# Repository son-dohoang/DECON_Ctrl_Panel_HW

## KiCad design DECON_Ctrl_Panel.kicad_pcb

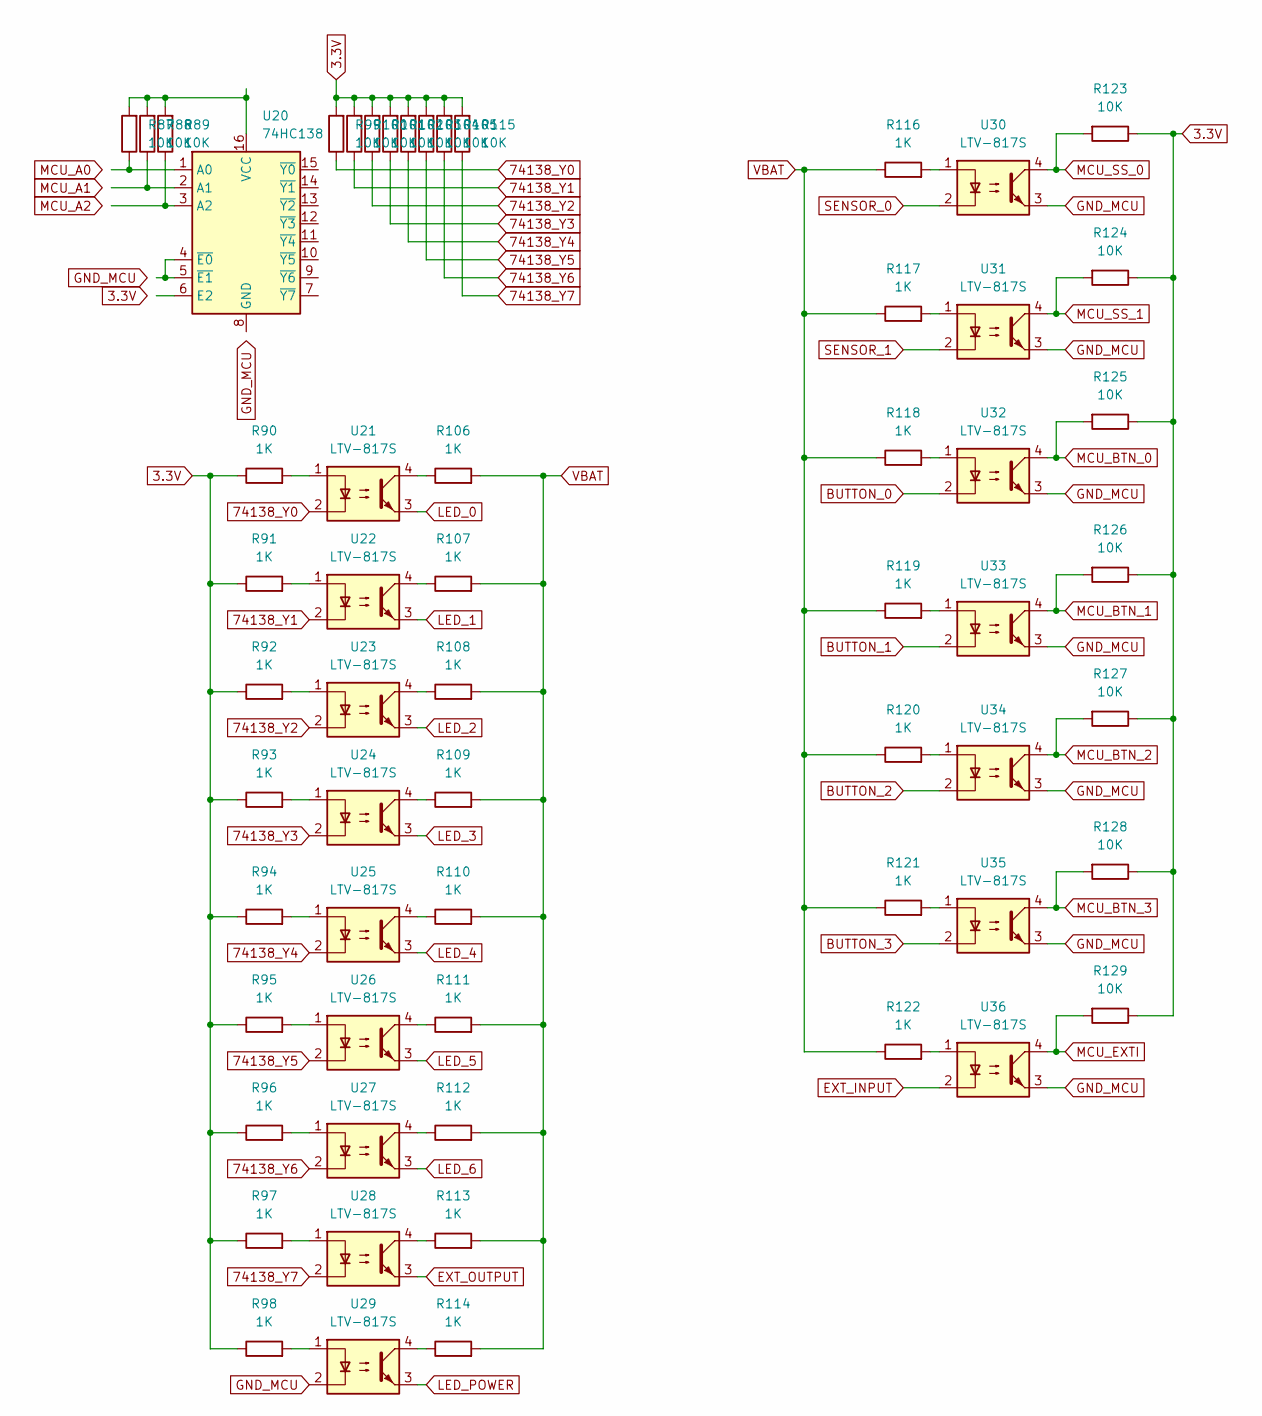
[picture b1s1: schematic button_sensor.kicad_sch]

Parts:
R87, R88, R89, R99, R100, R101, R102, R103, R104, R105, R115, R123, R124, R125, R126, R127, R128, R129: 10K; R_0805_2012Metric
R90, R91, R92, R93, R94, R95, R96, R97, R98, R106, R107, R108, R109, R110, R111, R112, R113, R114, R116, R117, R118, R119, R120, R121, R122: 1K; R_0805_2012Metric
U20: 74HC138; SOIC-16_3.9x9.9mm_P1.27mm
U21, U22, U23, U24, U25, U26, U27, U28, U29, U30, U31, U32, U33, U34, U35, U36: LTV-817S; SMDIP-4_W9.53mm

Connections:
3.3V: R90.1, R91.1, R92.1, R93.1, R94.1, R95.1, R96.1, R97.1, R98.1, R99.2, R100.2, R101.2, R102.2, R103.2, R104.2, R105.2, R115.2, R123.1, R124.1, R125.1, R126.1, R127.1, R128.1, R129.1; also elsewhere on the board
74138_Y0: R99.1, U21.2; also elsewhere on the board
74138_Y1: R100.1, U22.2; also elsewhere on the board
74138_Y2: R101.1, U23.2; also elsewhere on the board
74138_Y3: R102.1, U24.2; also elsewhere on the board
74138_Y4: R103.1, U25.2; also elsewhere on the board
74138_Y5: R104.1, U26.2; also elsewhere on the board
74138_Y6: R105.1, U27.2; also elsewhere on the board
74138_Y7: R115.1, U28.2; also elsewhere on the board
BUTTON_0: U32.2; also elsewhere on the board
BUTTON_1: U33.2; also elsewhere on the board
BUTTON_2: U34.2; also elsewhere on the board
BUTTON_3: U35.2; also elsewhere on the board
EXT_INPUT: U36.2; also elsewhere on the board
EXT_OUTPUT: U28.3; also elsewhere on the board
GND_MCU: U29.2, U30.3, U31.3, U32.3, U33.3, U34.3, U35.3, U36.3; also elsewhere on the board
LED_0: U21.3; also elsewhere on the board
LED_1: U22.3; also elsewhere on the board
LED_2: U23.3; also elsewhere on the board
LED_3: U24.3; also elsewhere on the board
LED_4: U25.3; also elsewhere on the board
LED_5: U26.3; also elsewhere on the board
LED_6: U27.3; also elsewhere on the board
LED_POWER: U29.3; also elsewhere on the board
MCU_BTN_0: R125.2, U32.4; also elsewhere on the board
MCU_BTN_1: R126.2, U33.4; also elsewhere on the board
MCU_BTN_2: R127.2, U34.4; also elsewhere on the board
MCU_BTN_3: R128.2, U35.4; also elsewhere on the board
MCU_EXTI: R129.2, U36.4; also elsewhere on the board
MCU_SS_0: R123.2, U30.4; also elsewhere on the board
MCU_SS_1: R124.2, U31.4; also elsewhere on the board
unnamed: R87.1, U20.1 (A0)
unnamed: R87.2, R88.2, R89.2, U20.16 (VCC)
unnamed: R88.1, U20.2 (A1)
unnamed: R89.1, U20.3 (A2)
unnamed: R90.2, U21.1
unnamed: R91.2, U22.1
unnamed: R92.2, U23.1
unnamed: R93.2, U24.1
unnamed: R94.2, U25.1
unnamed: R95.2, U26.1
unnamed: R96.2, U27.1
unnamed: R97.2, U28.1
unnamed: R98.2, U29.1
unnamed: R106.1, U21.4
unnamed: R107.1, U22.4
unnamed: R108.1, U23.4
unnamed: R109.1, U24.4
unnamed: R110.1, U25.4
unnamed: R111.1, U26.4
unnamed: R112.1, U27.4
unnamed: R113.1, U28.4
unnamed: R114.1, U29.4
unnamed: R116.2, U30.1
unnamed: R117.2, U31.1
unnamed: R118.2, U32.1
unnamed: R119.2, U33.1
unnamed: R120.2, U34.1
unnamed: R121.2, U35.1
unnamed: R122.2, U36.1
unnamed: U20.4 (~E0), U20.5 (~E1)
SENSOR_0: U30.2; also elsewhere on the board
SENSOR_1: U31.2; also elsewhere on the board
VBAT: R106.2, R107.2, R108.2, R109.2, R110.2, R111.2, R112.2, R113.2, R114.2, R116.1, R117.1, R118.1, R119.1, R120.1, R121.1, R122.1; also elsewhere on the board

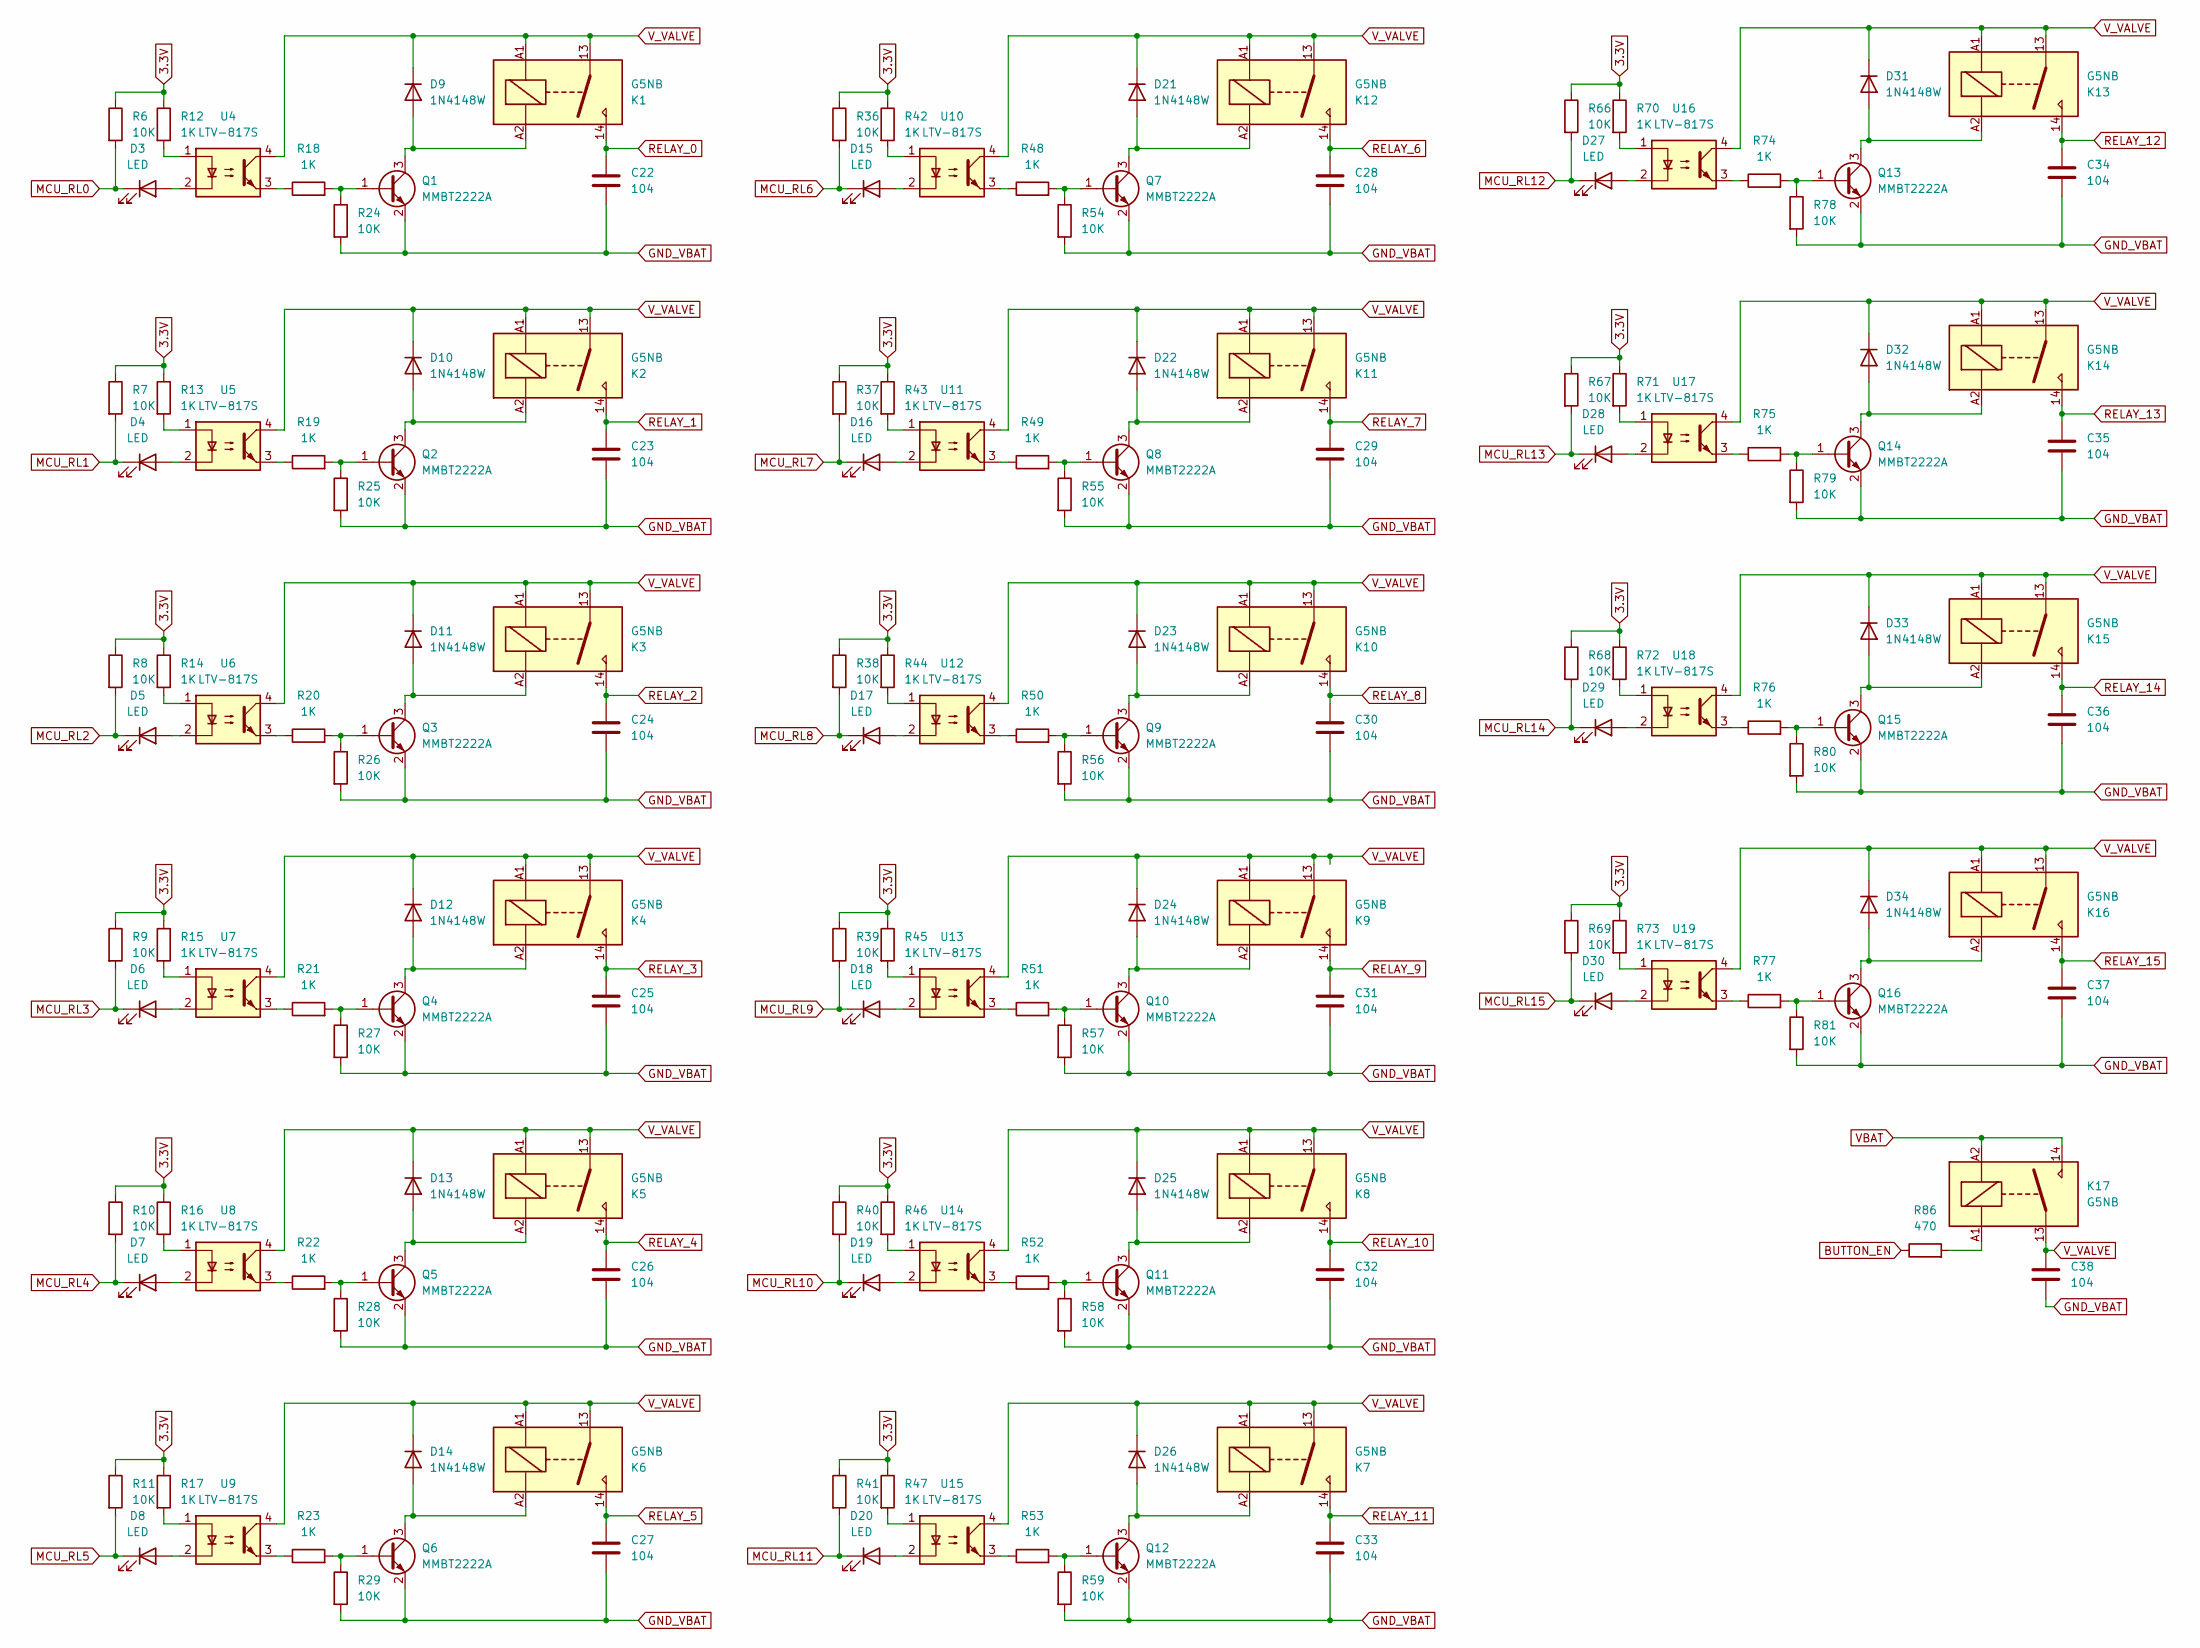
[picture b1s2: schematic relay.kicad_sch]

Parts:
C22, C23, C24, C25, C26, C27, C28, C29, C30, C31, C32, C33, C34, C35, C36, C37, C38: 104; C_0805_2012Metric
D3, D4, D5, D6, D7, D8, D15, D16, D17, D18, D19, D20, D27, D28, D29, D30: LED; LED_0805_2012Metric
D9, D10, D11, D12, D13, D14, D21, D22, D23, D24, D25, D26, D31, D32, D33, D34: 1N4148W; D_SOD-123
K1, K2, K3, K4, K5, K6, K7, K8, K9, K10, K11, K12, K13, K14, K15, K16, K17: G5NB; Relay_SPST_Omron_G5NB
Q1, Q2, Q3, Q4, Q5, Q6, Q7, Q8, Q9, Q10, Q11, Q12, Q13, Q14, Q15, Q16: MMBT2222A; SOT-23-3
R6, R7, R8, R9, R10, R11, R24, R25, R26, R27, R28, R29, R36, R37, R38, R39, R40, R41, R54, R55, R56, R57, R58, R59, R66, R67, R68, R69, R78, R79, R80, R81: 10K; R_0805_2012Metric
R12, R13, R14, R15, R16, R17, R18, R19, R20, R21, R22, R23, R42, R43, R44, R45, R46, R47, R48, R49, R50, R51, R52, R53, R70, R71, R72, R73, R74, R75, R76, R77: 1K; R_0805_2012Metric
R86: 470; R_0805_2012Metric
U4, U5, U6, U7, U8, U9, U10, U11, U12, U13, U14, U15, U16, U17, U18, U19: LTV-817S; SMDIP-4_W9.53mm

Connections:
3.3V: R6.1, R7.1, R8.1, R9.1, R10.1, R11.1, R12.1, R13.1, R14.1, R15.1, R16.1, R17.1, R36.1, R37.1, R38.1, R39.1, R40.1, R41.1, R42.1, R43.1, R44.1, R45.1, R46.1, R47.1, R66.1, R67.1, R68.1, R69.1, R70.1, R71.1, R72.1, R73.1; also elsewhere on the board
BUTTON_EN: R86.1; also elsewhere on the board
GND_VBAT: C22.2, C23.2, C24.2, C25.2, C26.2, C27.2, C28.2, C29.2, C30.2, C31.2, C32.2, C33.2, C34.2, C35.2, C36.2, C37.2, C38.2, Q1.2 (E), Q2.2 (E), Q3.2 (E), Q4.2 (E), Q5.2 (E), Q6.2 (E), Q7.2 (E), Q8.2 (E), Q9.2 (E), Q10.2 (E), Q11.2 (E), Q12.2 (E), Q13.2 (E), Q14.2 (E), Q15.2 (E), Q16.2 (E), R24.2, R25.2, R26.2, R27.2, R28.2, R29.2, R54.2, R55.2, R56.2, R57.2, R58.2, R59.2, R78.2, R79.2, R80.2, R81.2; also elsewhere on the board
MCU_RL0: D3.1 (K), R6.2; also elsewhere on the board
MCU_RL1: D4.1 (K), R7.2; also elsewhere on the board
MCU_RL2: D5.1 (K), R8.2; also elsewhere on the board
MCU_RL3: D6.1 (K), R9.2; also elsewhere on the board
MCU_RL4: D7.1 (K), R10.2; also elsewhere on the board
MCU_RL5: D8.1 (K), R11.2; also elsewhere on the board
MCU_RL6: D15.1 (K), R36.2; also elsewhere on the board
MCU_RL7: D16.1 (K), R37.2; also elsewhere on the board
MCU_RL8: D17.1 (K), R38.2; also elsewhere on the board
MCU_RL9: D18.1 (K), R39.2; also elsewhere on the board
MCU_RL10: D19.1 (K), R40.2; also elsewhere on the board
MCU_RL11: D20.1 (K), R41.2; also elsewhere on the board
MCU_RL12: D27.1 (K), R66.2; also elsewhere on the board
MCU_RL13: D28.1 (K), R67.2; also elsewhere on the board
MCU_RL14: D29.1 (K), R68.2; also elsewhere on the board
MCU_RL15: D30.1 (K), R69.2; also elsewhere on the board
unnamed: D3.2 (A), U4.2
unnamed: D4.2 (A), U5.2
unnamed: D5.2 (A), U6.2
unnamed: D6.2 (A), U7.2
unnamed: D7.2 (A), U8.2
unnamed: D8.2 (A), U9.2
unnamed: D9.2 (A), K1.A2, Q1.3 (C)
unnamed: D10.2 (A), K2.A2, Q2.3 (C)
unnamed: D11.2 (A), K3.A2, Q3.3 (C)
unnamed: D12.2 (A), K4.A2, Q4.3 (C)
unnamed: D13.2 (A), K5.A2, Q5.3 (C)
unnamed: D14.2 (A), K6.A2, Q6.3 (C)
unnamed: D15.2 (A), U10.2
unnamed: D16.2 (A), U11.2
unnamed: D17.2 (A), U12.2
unnamed: D18.2 (A), U13.2
unnamed: D19.2 (A), U14.2
unnamed: D20.2 (A), U15.2
unnamed: D21.2 (A), K12.A2, Q7.3 (C)
unnamed: D22.2 (A), K11.A2, Q8.3 (C)
unnamed: D23.2 (A), K10.A2, Q9.3 (C)
unnamed: D24.2 (A), K9.A2, Q10.3 (C)
unnamed: D25.2 (A), K8.A2, Q11.3 (C)
unnamed: D26.2 (A), K7.A2, Q12.3 (C)
unnamed: D27.2 (A), U16.2
unnamed: D28.2 (A), U17.2
unnamed: D29.2 (A), U18.2
unnamed: D30.2 (A), U19.2
unnamed: D31.2 (A), K13.A2, Q13.3 (C)
unnamed: D32.2 (A), K14.A2, Q14.3 (C)
unnamed: D33.2 (A), K15.A2, Q15.3 (C)
unnamed: D34.2 (A), K16.A2, Q16.3 (C)
unnamed: K17.A1, R86.2
unnamed: Q1.1 (B), R18.2, R24.1
unnamed: Q2.1 (B), R19.2, R25.1
unnamed: Q3.1 (B), R20.2, R26.1
unnamed: Q4.1 (B), R21.2, R27.1
unnamed: Q5.1 (B), R22.2, R28.1
unnamed: Q6.1 (B), R23.2, R29.1
unnamed: Q7.1 (B), R48.2, R54.1
unnamed: Q8.1 (B), R49.2, R55.1
unnamed: Q9.1 (B), R50.2, R56.1
unnamed: Q10.1 (B), R51.2, R57.1
unnamed: Q11.1 (B), R52.2, R58.1
unnamed: Q12.1 (B), R53.2, R59.1
unnamed: Q13.1 (B), R74.2, R78.1
unnamed: Q14.1 (B), R75.2, R79.1
unnamed: Q15.1 (B), R76.2, R80.1
unnamed: Q16.1 (B), R77.2, R81.1
unnamed: R12.2, U4.1
unnamed: R13.2, U5.1
unnamed: R14.2, U6.1
unnamed: R15.2, U7.1
unnamed: R16.2, U8.1
unnamed: R17.2, U9.1
unnamed: R18.1, U4.3
unnamed: R19.1, U5.3
unnamed: R20.1, U6.3
unnamed: R21.1, U7.3
unnamed: R22.1, U8.3
unnamed: R23.1, U9.3
unnamed: R42.2, U10.1
unnamed: R43.2, U11.1
unnamed: R44.2, U12.1
unnamed: R45.2, U13.1
unnamed: R46.2, U14.1
unnamed: R47.2, U15.1
unnamed: R48.1, U10.3
unnamed: R49.1, U11.3
unnamed: R50.1, U12.3
unnamed: R51.1, U13.3
unnamed: R52.1, U14.3
unnamed: R53.1, U15.3
unnamed: R70.2, U16.1
unnamed: R71.2, U17.1
unnamed: R72.2, U18.1
unnamed: R73.2, U19.1
unnamed: R74.1, U16.3
unnamed: R75.1, U17.3
unnamed: R76.1, U18.3
unnamed: R77.1, U19.3
RELAY_0: C22.1, K1.14; also elsewhere on the board
RELAY_1: C23.1, K2.14; also elsewhere on the board
RELAY_2: C24.1, K3.14; also elsewhere on the board
RELAY_3: C25.1, K4.14; also elsewhere on the board
RELAY_4: C26.1, K5.14; also elsewhere on the board
RELAY_5: C27.1, K6.14; also elsewhere on the board
RELAY_6: C28.1, K12.14; also elsewhere on the board
RELAY_7: C29.1, K11.14; also elsewhere on the board
RELAY_8: C30.1, K10.14; also elsewhere on the board
RELAY_9: C31.1, K9.14; also elsewhere on the board
RELAY_10: C32.1, K8.14; also elsewhere on the board
RELAY_11: C33.1, K7.14; also elsewhere on the board
RELAY_12: C34.1, K13.14; also elsewhere on the board
RELAY_13: C35.1, K14.14; also elsewhere on the board
RELAY_14: C36.1, K15.14; also elsewhere on the board
RELAY_15: C37.1, K16.14; also elsewhere on the board
VBAT: K17.14, K17.A2; also elsewhere on the board
V_VALVE: C38.1, D9.1 (K), D10.1 (K), D11.1 (K), D12.1 (K), D13.1 (K), D14.1 (K), D21.1 (K), D22.1 (K), D23.1 (K), D24.1 (K), D25.1 (K), D26.1 (K), D31.1 (K), D32.1 (K), D33.1 (K), D34.1 (K), K1.13, K1.A1, K2.13, K2.A1, K3.13, K3.A1, K4.13, K4.A1, K5.13, K5.A1, K6.13, K6.A1, K7.13, K7.A1, K8.13, K8.A1, K9.13, K9.A1, K10.13, K10.A1, K11.13, K11.A1, K12.13, K12.A1, K13.13, K13.A1, K14.13, K14.A1, K15.13, K15.A1, K16.13, K16.A1, K17.13, U4.4, U5.4, U6.4, U7.4, U8.4, U9.4, U10.4, U11.4, U12.4, U13.4, U14.4, U15.4, U16.4, U17.4, U18.4, U19.4

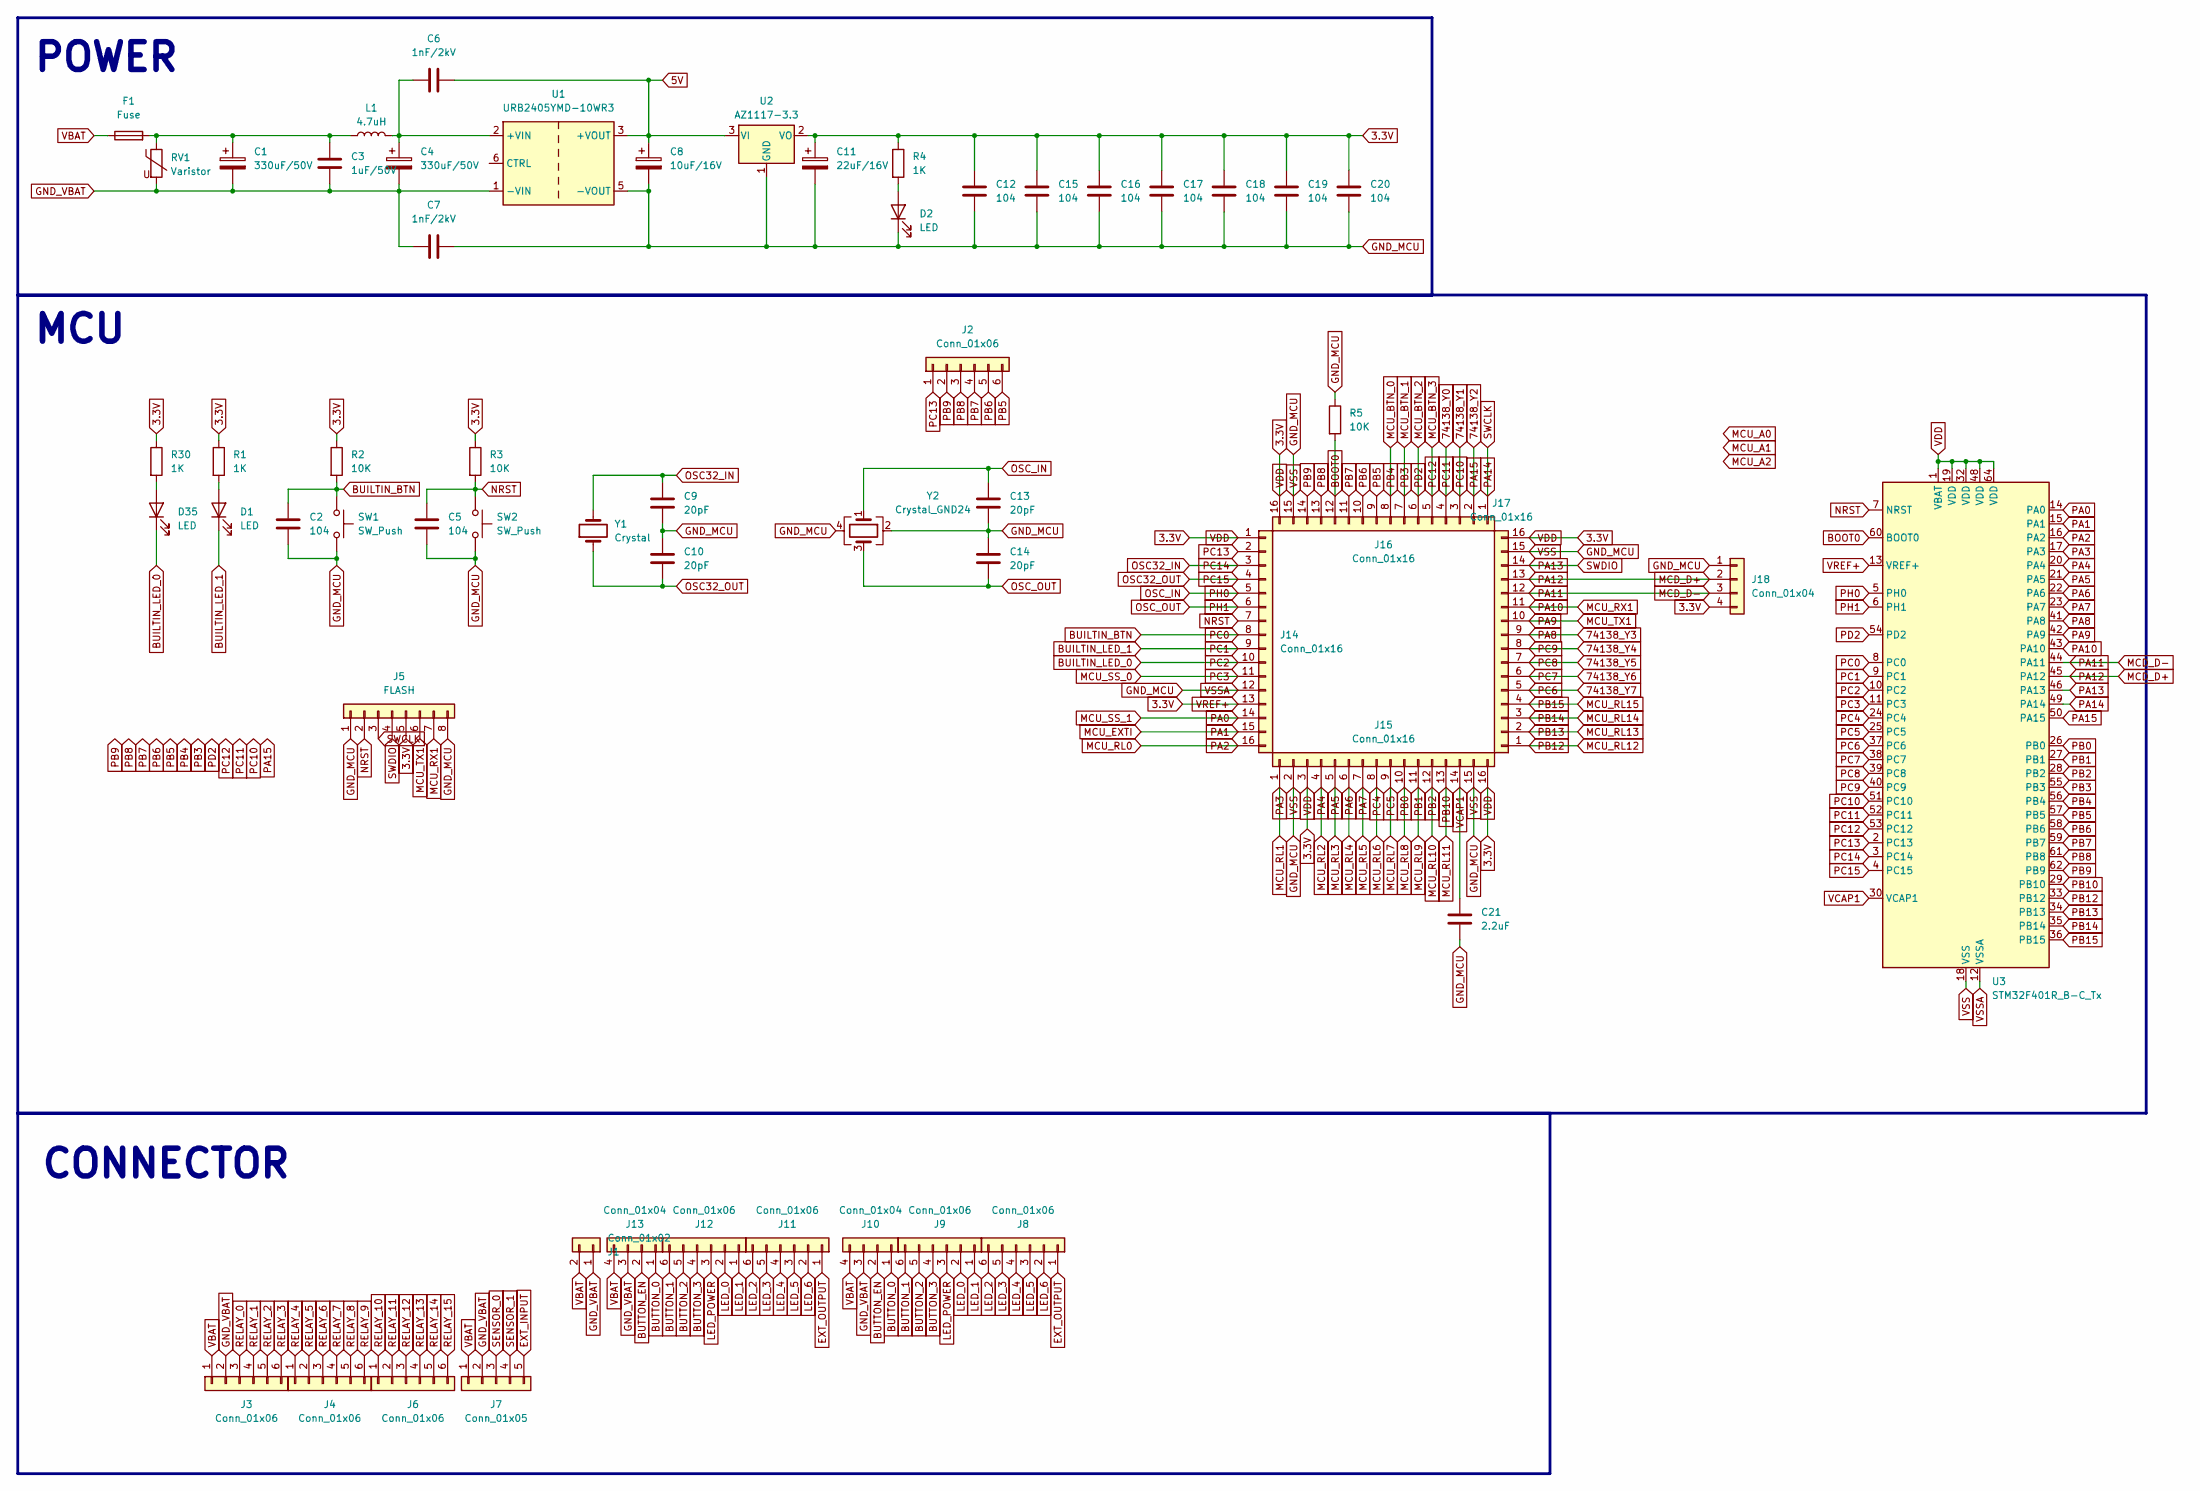
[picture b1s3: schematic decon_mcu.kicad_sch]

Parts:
C1, C4: 330uF/50V; CP_Elec_10x10.5
C2, C5, C12, C15, C16, C17, C18, C19, C20: 104; C_0805_2012Metric
C3: 1uF/50V; C_0805_2012Metric
C6, C7: 1nF/2kV; C_Disc_D5.0mm_W2.5mm_P5.00mm
C8: 10uF/16V; CP_Elec_4x5.4
C9, C10, C13, C14: 20pF; C_0805_2012Metric
C11: 22uF/16V; CP_Elec_4x5.4
C21: 2.2uF; C_0805_2012Metric
D1, D2, D35: LED; LED_0805_2012Metric
F1: Fuse; Fuseholder_Clip-5x20mm_Eaton_1A5601-01_Inline_P20.80x6.76mm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
J1: Conn_01x02; TerminalBlock_MetzConnect_Type086_RT03402HBLC_1x02_P3.81mm_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
J2: Conn_01x06; PinHeader_1x06_P2.54mm_Vertical
J3, J4, J6, J8, J9, J11, J12: Conn_01x06; TerminalBlock_MetzConnect_Type086_RT03406HBLC_1x06_P3.81mm_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
J5: FLASH; PinHeader_1x08_P2.54mm_Vertical
J7: Conn_01x05; TerminalBlock_MetzConnect_Type086_RT03405HBLC_1x05_P3.81mm_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
J10, J13: Conn_01x04; TerminalBlock_MetzConnect_Type086_RT03404HBLC_1x04_P3.81mm_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
J14, J15, J16, J17: Conn_01x16
J18: Conn_01x04; PinHeader_1x04_P2.54mm_Vertical
L1: 4.7uH; L_APV_APH0630
R1, R4, R30: 1K; R_0805_2012Metric
R2, R3, R5: 10K; R_0805_2012Metric
RV1: Varistor; RV_Disc_D7mm_W3.4mm_P5mm
SW1, SW2: SW_Push; SW_SPST_CK_RS282G05A3
U1: URB2405YMD-10WR3
U2: AZ1117-3.3; SOT-223-3_TabPin2
U3: STM32F401R_B-C_Tx; LQFP-64_10x10mm_P0.5mm
Y1: Crystal; Crystal_SMD_3215-2Pin_3.2x1.5mm
Y2: Crystal_GND24; Crystal_SMD_3225-4Pin_3.2x2.5mm

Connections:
3.3V: C11.1, C12.2, C15.2, C16.2, C17.2, C18.2, C19.2, C20.2, J5.5, J14.1, J14.13, J15.3, J15.16, J16.16, J17.16, J18.4, R1.1, R2.1, R3.1, R4.1, R30.1, U2.2 (VO), U3.1 (VBAT), U3.13 (VREF+), U3.19 (VDD), U3.32 (VDD), U3.48 (VDD), U3.64 (VDD); also elsewhere on the board
5V: C6.2, C8.1, U1.3 (+VOUT), U2.3 (VI)
74138_Y0: J16.4, U3.52 (PC11); also elsewhere on the board
74138_Y1: J16.3, U3.51 (PC10); also elsewhere on the board
74138_Y2: J16.2, U3.50 (PA15); also elsewhere on the board
74138_Y3: J17.9, U3.41 (PA8); also elsewhere on the board
74138_Y4: J17.8, U3.40 (PC9); also elsewhere on the board
74138_Y5: J17.7, U3.39 (PC8); also elsewhere on the board
74138_Y6: J17.6, U3.38 (PC7); also elsewhere on the board
74138_Y7: J17.5, U3.37 (PC6); also elsewhere on the board
BOOT0: J16.12, R5.2, U3.60 (BOOT0)
BUILTIN_BTN: C2.1, J14.8, R2.2, SW1.1, U3.8 (PC0)
BUILTIN_LED_0: D35.1 (K), J14.10, U3.10 (PC2)
BUILTIN_LED_1: D1.1 (K), J14.9, U3.9 (PC1)
BUTTON_0: J10.1, J13.1; also elsewhere on the board
BUTTON_1: J9.6, J12.6; also elsewhere on the board
BUTTON_2: J9.5, J12.5; also elsewhere on the board
BUTTON_3: J9.4, J12.4; also elsewhere on the board
BUTTON_EN: J10.2, J13.2; also elsewhere on the board
EXT_INPUT: J7.5; also elsewhere on the board
EXT_OUTPUT: J8.1, J11.1; also elsewhere on the board
GND_MCU: C2.2, C5.2, C7.2, C8.2, C9.2, C10.1, C11.2, C12.1, C13.1, C14.1, C15.1, C16.1, C17.1, C18.1, C19.1, C20.1, C21.2, D2.1 (K), J5.1, J5.8, J14.12, J15.2, J15.15, J16.15, J17.15, J18.1, R5.1, SW1.2, SW2.2, U1.5 (-VOUT), U2.1 (GND), U3.12 (VSSA), U3.18 (VSS), U3.31 (VSS), U3.47 (VSS), U3.63 (VSS), Y2.2, Y2.4; also elsewhere on the board
GND_VBAT: C1.2, C3.2, C4.2, C7.1, J1.1, J3.2, J7.2, J10.3, J13.3, RV1.2, U1.1 (-VIN); also elsewhere on the board
LED_0: J9.2, J12.2; also elsewhere on the board
LED_1: J9.1, J12.1; also elsewhere on the board
LED_2: J8.6, J11.6; also elsewhere on the board
LED_3: J8.5, J11.5; also elsewhere on the board
LED_4: J8.4, J11.4; also elsewhere on the board
LED_5: J8.3, J11.3; also elsewhere on the board
LED_6: J8.2, J11.2; also elsewhere on the board
LED_POWER: J9.3, J12.3; also elsewhere on the board
MCD_D+: J17.13, J18.2, U3.45 (PA12)
MCD_D-: J17.12, J18.3, U3.44 (PA11)
MCU_BTN_0: J16.8, U3.56 (PB4); also elsewhere on the board
MCU_BTN_1: J16.7, U3.55 (PB3); also elsewhere on the board
MCU_BTN_2: J16.6, U3.54 (PD2); also elsewhere on the board
MCU_BTN_3: J16.5, U3.53 (PC12); also elsewhere on the board
MCU_EXTI: J14.15, U3.15 (PA1); also elsewhere on the board
MCU_RL0: J14.16, U3.16 (PA2); also elsewhere on the board
MCU_RL1: J15.1, U3.17 (PA3); also elsewhere on the board
MCU_RL2: J15.4, U3.20 (PA4); also elsewhere on the board
MCU_RL3: J15.5, U3.21 (PA5); also elsewhere on the board
MCU_RL4: J15.6, U3.22 (PA6); also elsewhere on the board
MCU_RL5: J15.7, U3.23 (PA7); also elsewhere on the board
MCU_RL6: J15.8, U3.24 (PC4); also elsewhere on the board
MCU_RL7: J15.9, U3.25 (PC5); also elsewhere on the board
MCU_RL8: J15.10, U3.26 (PB0); also elsewhere on the board
MCU_RL9: J15.11, U3.27 (PB1); also elsewhere on the board
MCU_RL10: J15.12, U3.28 (PB2); also elsewhere on the board
MCU_RL11: J15.13, U3.29 (PB10); also elsewhere on the board
MCU_RL12: J17.1, U3.33 (PB12); also elsewhere on the board
MCU_RL13: J17.2, U3.34 (PB13); also elsewhere on the board
MCU_RL14: J17.3, U3.35 (PB14); also elsewhere on the board
MCU_RL15: J17.4, U3.36 (PB15); also elsewhere on the board
MCU_RX1: J5.7, J17.11, U3.43 (PA10)
MCU_SS_0: J14.11, U3.11 (PC3); also elsewhere on the board
MCU_SS_1: J14.14, U3.14 (PA0); also elsewhere on the board
MCU_TX1: J5.6, J17.10, U3.42 (PA9)
NRST: C5.1, J5.2, J14.7, R3.2, SW2.1, U3.7 (NRST)
unnamed: C1.1, C3.1, F1.2, L1.1, RV1.1
unnamed: D1.2 (A), R1.2
unnamed: D2.2 (A), R4.2
unnamed: D35.2 (A), R30.2
unnamed: C4.1, C6.1, L1.2, U1.2 (+VIN)
OSC32_IN: C9.1, J14.3, U3.3 (PC14), Y1.2
OSC32_OUT: C10.2, J14.4, U3.4 (PC15), Y1.1
OSC_IN: C13.2, J14.5, U3.5 (PH0), Y2.1
OSC_OUT: C14.2, J14.6, U3.6 (PH1), Y2.3
PA13: J5.4, J17.14, U3.46 (PA13)
PA14: J5.3, J16.1, U3.49 (PA14)
PB5: J2.6, J16.9, U3.57 (PB5)
PB6: J2.5, J16.10, U3.58 (PB6)
PB7: J2.4, J16.11, U3.59 (PB7)
PB8: J2.3, J16.13, U3.61 (PB8)
PB9: J2.2, J16.14, U3.62 (PB9)
PC13: J2.1, J14.2, U3.2 (PC13)
RELAY_0: J3.3; also elsewhere on the board
RELAY_1: J3.4; also elsewhere on the board
RELAY_2: J3.5; also elsewhere on the board
RELAY_3: J3.6; also elsewhere on the board
RELAY_4: J4.1; also elsewhere on the board
RELAY_5: J4.2; also elsewhere on the board
RELAY_6: J4.3; also elsewhere on the board
RELAY_7: J4.4; also elsewhere on the board
RELAY_8: J4.5; also elsewhere on the board
RELAY_9: J4.6; also elsewhere on the board
RELAY_10: J6.1; also elsewhere on the board
RELAY_11: J6.2; also elsewhere on the board
RELAY_12: J6.3; also elsewhere on the board
RELAY_13: J6.4; also elsewhere on the board
RELAY_14: J6.5; also elsewhere on the board
RELAY_15: J6.6; also elsewhere on the board
SENSOR_0: J7.3; also elsewhere on the board
SENSOR_1: J7.4; also elsewhere on the board
VBAT: F1.1, J1.2, J3.1, J7.1, J10.4, J13.4; also elsewhere on the board
VCAP1: C21.1, J15.14, U3.30 (VCAP1)

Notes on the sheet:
CONNECTOR
POWER
MCU

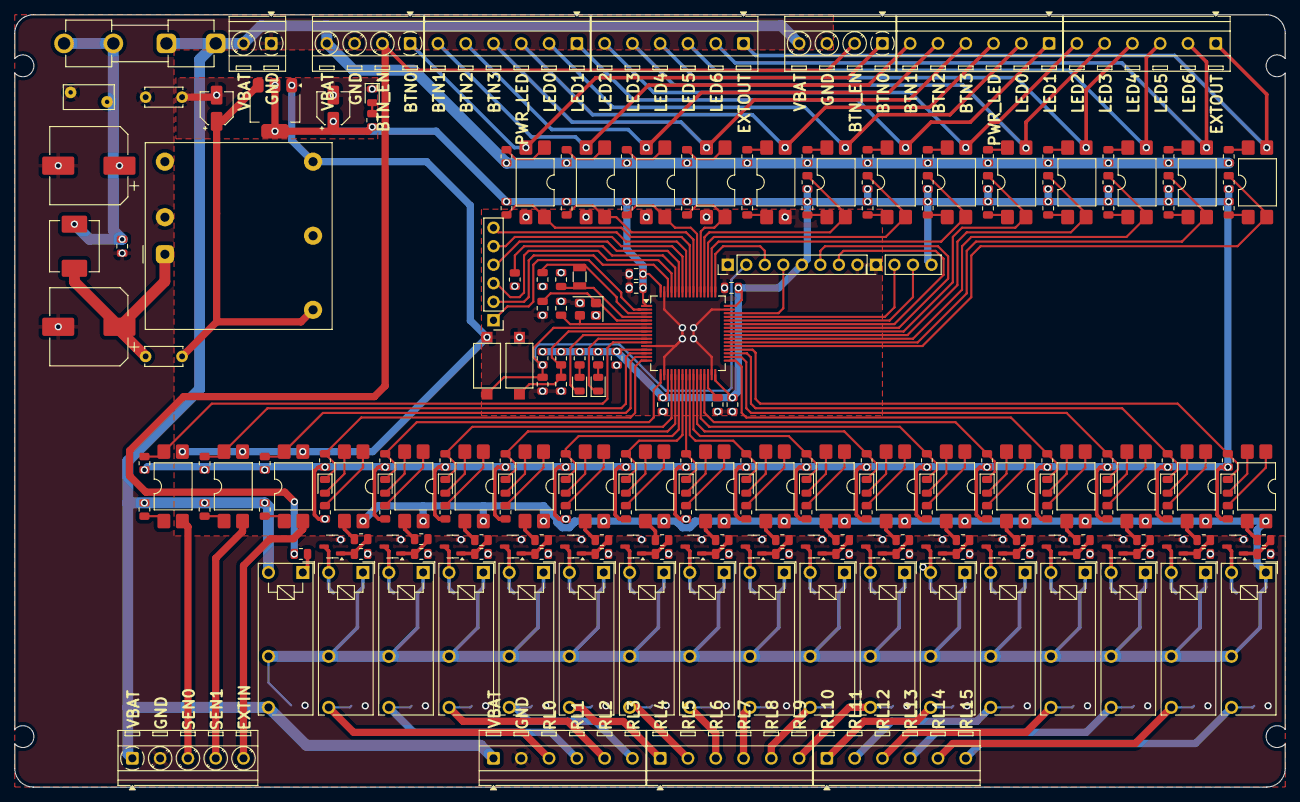
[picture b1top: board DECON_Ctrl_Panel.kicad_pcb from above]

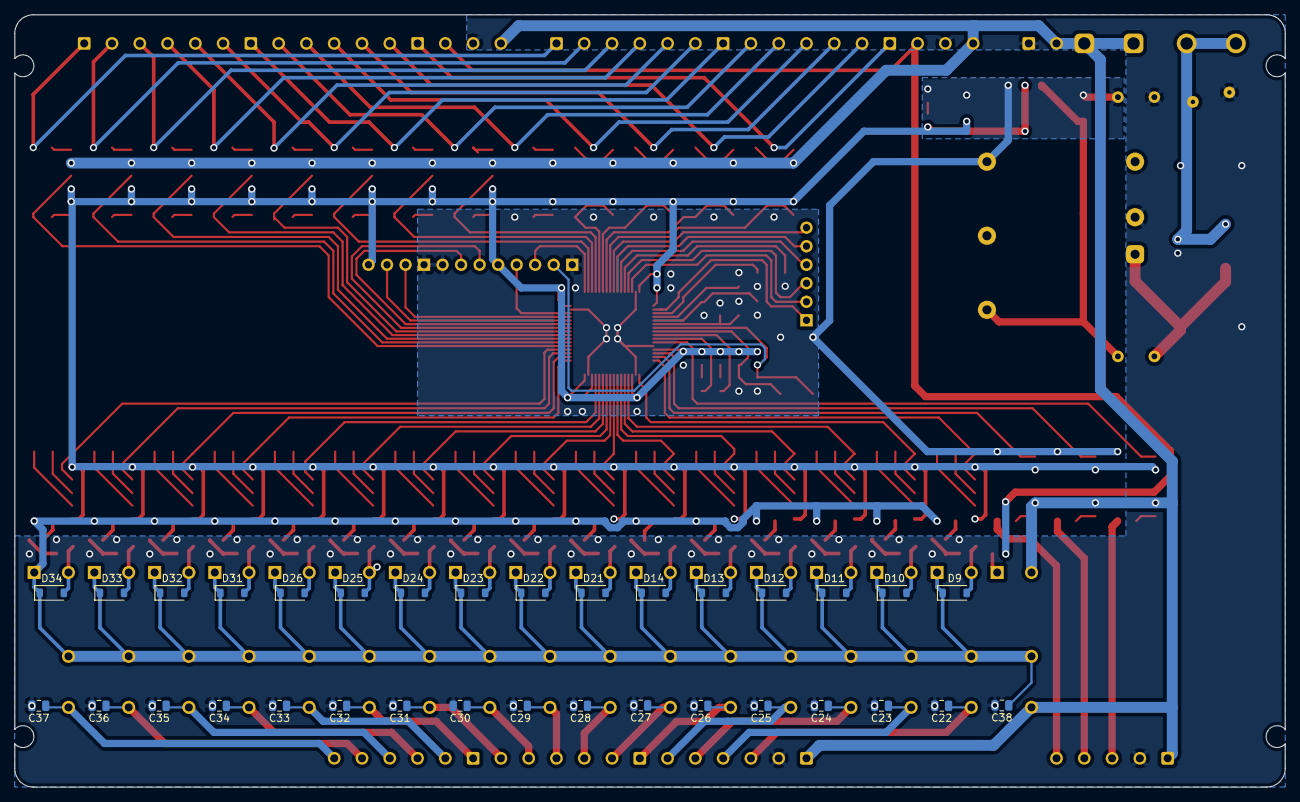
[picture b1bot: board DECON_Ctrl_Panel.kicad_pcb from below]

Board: 2 copper layers, 174.2 x 105.9 mm, 272 parts (33 on the bottom side), 203 nets.

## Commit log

2025-10-20 init repo
2025-10-20 modified: DECON_Ctrl_Panel.kicad_pcb modified: DECON_Ctrl_Panel.kicad_prl new file: MCU_pins.xlsx new file: Son_KiCad_lib/Son_KiCad_lib.bak new file: Son_KiCad_lib/Son_KiCad_lib.kicad_sym new file: S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
2025-10-20 modified: .gitignore new file: fp-info-cache
2025-10-20 modified: DECON_Ctrl_Panel.kicad_sch
2025-10-21 new file: decon_ctrl.pdf
2025-10-21 modified: DECON_Ctrl_Panel.kicad_pcb
2025-10-26 modified: DECON_Ctrl_Panel.kicad_prl
2025-10-26 modified: DECON_Ctrl_Panel.kicad_pcb modified: DECON_Ctrl_Panel.kicad_prl modified: decon_mcu.kicad_sch
2025-10-27 modified: DECON_Ctrl_Panel.kicad_pcb modified: DECON_Ctrl_Panel.kicad_prl modified: DECON_Ctrl_Panel.kicad_pro
2025-10-29 modified: DECON_Ctrl_Panel.kicad_pcb modified: DECON_Ctrl_Panel.kicad_prl modified: button_sensor.kicad_sch modified: decon_mcu.kicad_sch
2025-10-30 modified: DECON_Ctrl_Panel.kicad_pcb modified: DECON_Ctrl_Panel.kicad_prl modified: decon_mcu.kicad_sch modified: fp-info-cache
2025-10-31 modified: DECON_Ctrl_Panel.kicad_pcb modified: DECON_Ctrl_Panel.kicad_prl new file: Fuseholder_Clip-5x20mm_Eaton_1A5601-01_Inline_P20.80x6.76mm_D1.70mm_Horizontal.STEP renamed: TerminalBlock_MetzConn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
2026-05-29 modified: DECON_Ctrl_Panel.kicad_pcb modified: DECON_Ctrl_Panel.kicad_prl modified: DECON_Ctrl_Panel.kicad_pro modified: decon_mcu.kicad_sch new file: decon_mcu.kicad_sch-bak modified: fp-info-cache 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
